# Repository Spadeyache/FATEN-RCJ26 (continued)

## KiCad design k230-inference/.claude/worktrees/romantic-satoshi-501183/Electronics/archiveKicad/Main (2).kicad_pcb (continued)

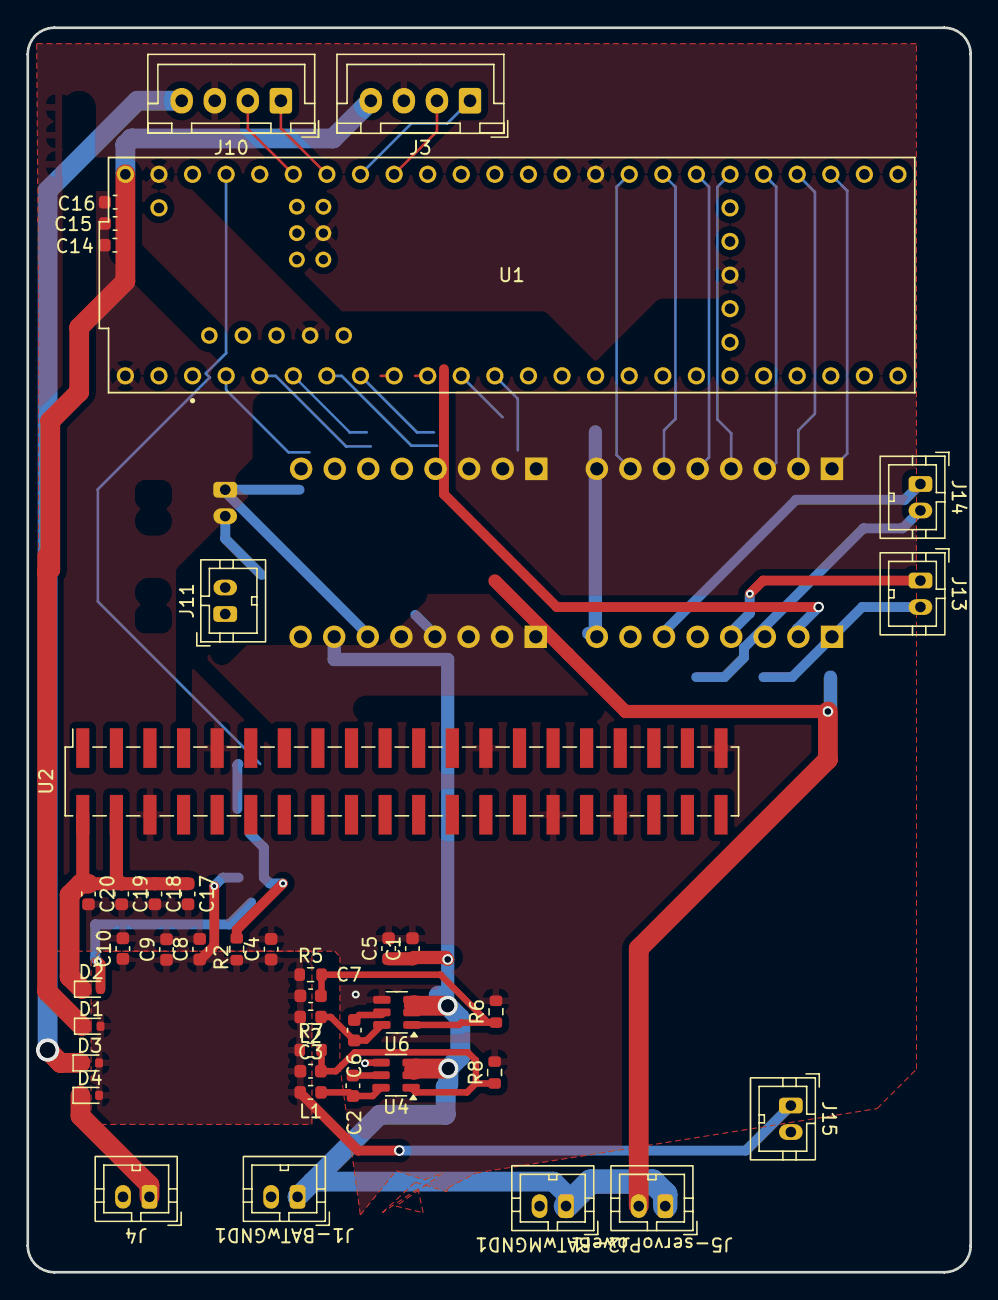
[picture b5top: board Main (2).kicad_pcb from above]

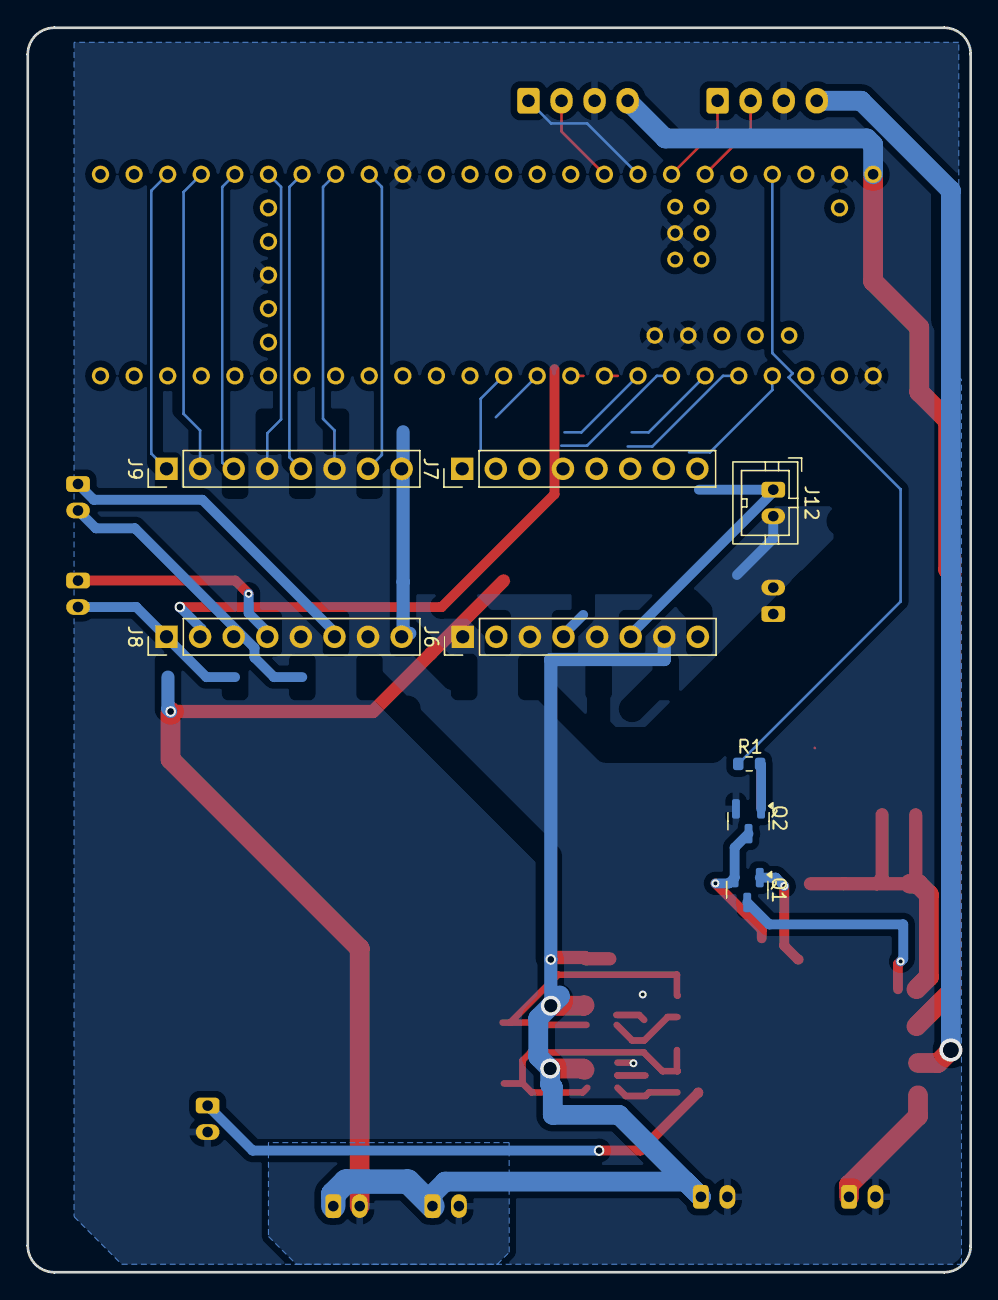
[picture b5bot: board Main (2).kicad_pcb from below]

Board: 2 copper layers, 71.3 x 94.1 mm, 50 parts (8 on the bottom side), 47 nets.

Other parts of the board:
D4: 1N4148WT; D_SOD-523
J4, J5-servoPower1, J15: Conn_01x02; TE_440054-2_1x02_P2.00mm_Vertical

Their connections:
+5.3V: D4.2 (A), J15.1; also elsewhere on the board
+6.6V: J5-servoPower1.1; also elsewhere on the board
GND: J4.2, J15.2; also elsewhere on the board
MGND: J5-servoPower1.2; also elsewhere on the board
unnamed: D4.1 (K), J4.1

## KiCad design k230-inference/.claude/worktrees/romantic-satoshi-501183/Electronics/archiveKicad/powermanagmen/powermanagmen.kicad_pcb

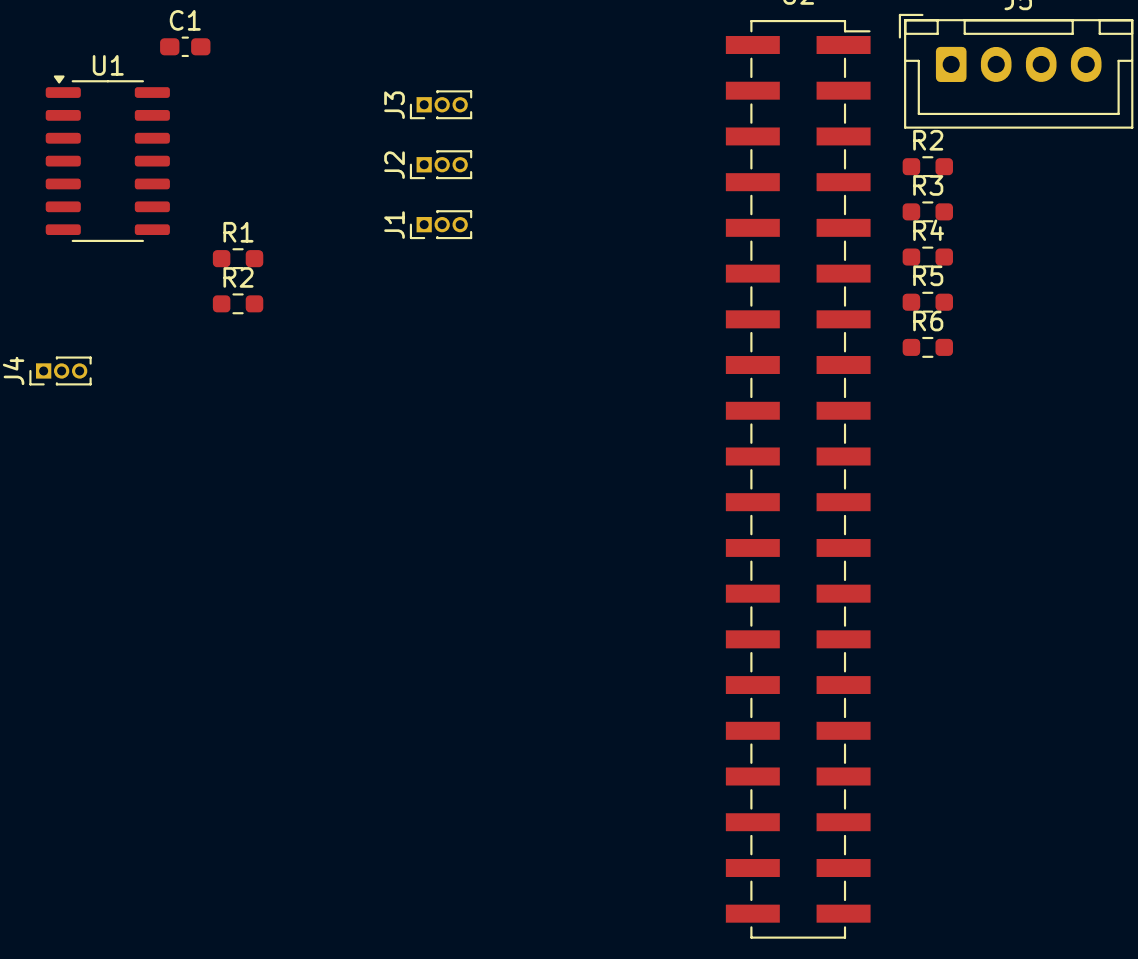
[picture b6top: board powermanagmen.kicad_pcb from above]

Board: 2 copper layers, 15 parts (0 on the bottom side), 8 nets, no tracks yet.

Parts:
C1: 0.1uF; C_0603_1608Metric_Pad1.08x0.95mm_HandSolder
J1: STS3032; PinHeader_1x03_P1.00mm_Vertical
J2: KRS3301; PinHeader_1x03_P1.00mm_Vertical
J3: HS45HB-0; PinHeader_1x03_P1.00mm_Vertical
J4: HS45HB-1; PinHeader_1x03_P1.00mm_Vertical
J5: IMU MPU6050; JST_XH_B4B-XH-A_1x04_P2.50mm_Vertical
R1, R2: 10k; R_0603_1608Metric_Pad0.98x0.95mm_HandSolder
R2#2, R3, R4, R5, R6: 10k?; R_0603_1608Metric_Pad0.98x0.95mm_HandSolder
U1: 74LS126; SOIC-14_3.9x8.7mm_P1.27mm
U2: K230D; PinSocket_2x20_P2.54mm_Vertical_SMD

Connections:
+5V: C1.2, J3.1, J4.1, U1.4, U1.10, U1.13, U1.14 (VCC)
+6.6V: J1.1, J2.1
GND: C1.1, J1.3, J2.3, J3.3, J4.3, J5.1, R1.1, U1.7 (GND)
HS45HB-0 signal: J3.2, U1.8
HS45HB-1 signal: J4.2, U1.11
KRS3301 signal: J2.2, U1.6
STS3032 signal: J1.2, U1.3
Teensy 2?: R1.2, U1.1

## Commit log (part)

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2026-05-08 yolo trained
2026-05-12 Add quant-aware weight finetuning to kmodel converter
    - convert_to_kmodel3.py: expose --finetune-weights flag (defaults to UseSquant)
    so PTQ runs nncase's quant-aware weight refinement. Recovers most of the
    confidence lost to int8/uint8 quantization without retraining.
    - summarize_workspace.py: small helper that prints a per-file summary of the
    workspace (docstrings + pipeline order).
    - yolo_training_explained.html: standalone reference doc covering the YOLO
2026-05-13 kmodel converting
2026-05-16 obstacle and ngi
2026-05-16 NGI and obs
2026-05-16 gap classification
2026-05-17 Add yolov5 training workspace files
2026-05-17 rcjusa
2026-05-19 kmodel quantized sumilation
2026-05-20 quantized kmodel sucseed
2026-05-21 pcb schematic completed
2026-05-22 PCB update
2026-05-22 breackout design done!
2026-05-22 part2 done
2026-05-23 teensy and pow update for international
2026-05-24 PCB ordere batch
2026-05-24 organized k230 train
2026-05-24 updated k230
2026-05-25 end2end train tested on DESK PC
2026-05-25 Restructure teensy/STS-imuMerge into layered src/ tree
2026-05-29 teensy restructure code
2026-05-30 working version
2026-05-31 testing
2026-05-31 upgraded planning
2026-05-31 docs
2026-06-01 hardware plan
2026-06-05 k230 config
2026-06-08 teensy update
2026-06-09 k230 communication
2026-06-09 k230 internally complete
2026-06-10 evacuation ball capture
2026-06-12 final before pivoting to new robot
2026-06-12 pin cofiguration
2026-06-12 confirmed operatino on newrobot with tuned parameters for flat line follow
2026-06-13 updaate
2026-06-13 clean up code pid and vibration removed
2026-06-17 update before starting a new line follow on xiao
2026-06-18 implementeing new xiao procceing
2026-06-18 implemented a working line following model
2026-06-19 added intersection contineous line follow
2026-06-19 line follow with green intersection updated teensy state control logic
2026-06-19 silver, red, gap detection implemented on xiao
2026-06-20 gap sequ3nce added
2026-06-20 update before restructure
2026-06-20 Saving my current work here
2026-06-20 tof moving
2026-06-21 tof wraper func
2026-06-21 delay to init tof is fixed
2026-06-21 push before editing line follow box
2026-06-21 beautiful line follow algorythm, circle box
2026-06-21 update before gap, red, green - silver was implemnted
2026-06-21 gap, red, green with cmd filter implemneted
2026-06-22 line following red detection verified!
2026-06-22 tilted line follow box
2026-06-22 before adding linefollow edge case.
2026-06-22 before starting AI train
2026-06-22 AI model trained
2026-06-23 ai model train restrucutre
2026-06-23 updated k230 ai train for competition ready. must solve AI run speed on chip. commiting before cleanning xiao
2026-06-23 new xiao structure
2026-06-23 working kmodel
2026-06-23 xiao best line follow. to be adding green and curve+intersection improvments
2026-06-23 supere improvment on linne following
2026-06-23 gap added. not verified
2026-06-23 added obstacle. not tested.
2026-06-24 not working but checkpoint line folow
2026-06-24 update not complete
2026-06-24 commit before going back
2026-06-25 line follow can now deal with twoo point
2026-06-25 every line exept +90 and 90,90,90, NoGI
2026-06-25 intersection added with cmd filter in xiao
2026-06-25 line following with gap to be improved
2026-06-26 update before
2026-06-26 krs PWM can HS45HB connected
2026-06-26 arm macros
2026-06-27 arm grabs
2026-06-27 commit before updating search
2026-06-27 working evac serach
2026-06-28 calibration values tuned
2026-06-28 comit before evac change
2026-06-28 evac logic and nogi added
2026-06-28 im happy wit thi ver
2026-06-28 added k230 code
2026-06-28 working evac seach / grab
2026-06-28 tuned storing for victim
2026-06-29 slope line follow, gap, obs update
2026-06-29 line evac mask
2026-06-29 clean line follow
2026-06-30 intersectio ntuned
2026-06-30 black evac end readings works
